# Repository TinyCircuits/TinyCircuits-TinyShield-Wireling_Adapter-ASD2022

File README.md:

# TinyCircuits TinyShield Wireling Adapter ASD2022
# ASD2022 Rev4

The design files are located under design_files/ for the TinyCircuits ASD2022 Rev 4 PCB. This is a TinyShield that is meant to add 4 separately addressable Wireling Ports to any TinyDuino stack.

Format is in Cadsoft Eagle format - Eagle version 6.2 was used for the original design.

For more infomation on this, check out the product page at TinyCircuits.com

# License:

Design by TinyCircuits.
All design files are released under the Creative Commons Attribution Share-Alike 3.0 License, see the following link for details: http://creativecommons.org/licenses/by-sa/3.0

All text above must be included in any redistribution or derived design

This project uses designs and concepts developed as part of the Arduino project and the LilyPad project.  The TinyCircuits design files themselves (schematics, PCB and libraries) are not directly derived from these works' design files and have been created new, however the concepts and basic architecture behind the TinyDuino and TinyLily products are derived and we thank the hard work of the organizations below for their contributions to open-source hardware:
  
Original Arduino Uno Design by Team Arduino

LilyPad Arduino Design by Leah Buechley and Sparkfun Electronics

Please support the open-source hardware community

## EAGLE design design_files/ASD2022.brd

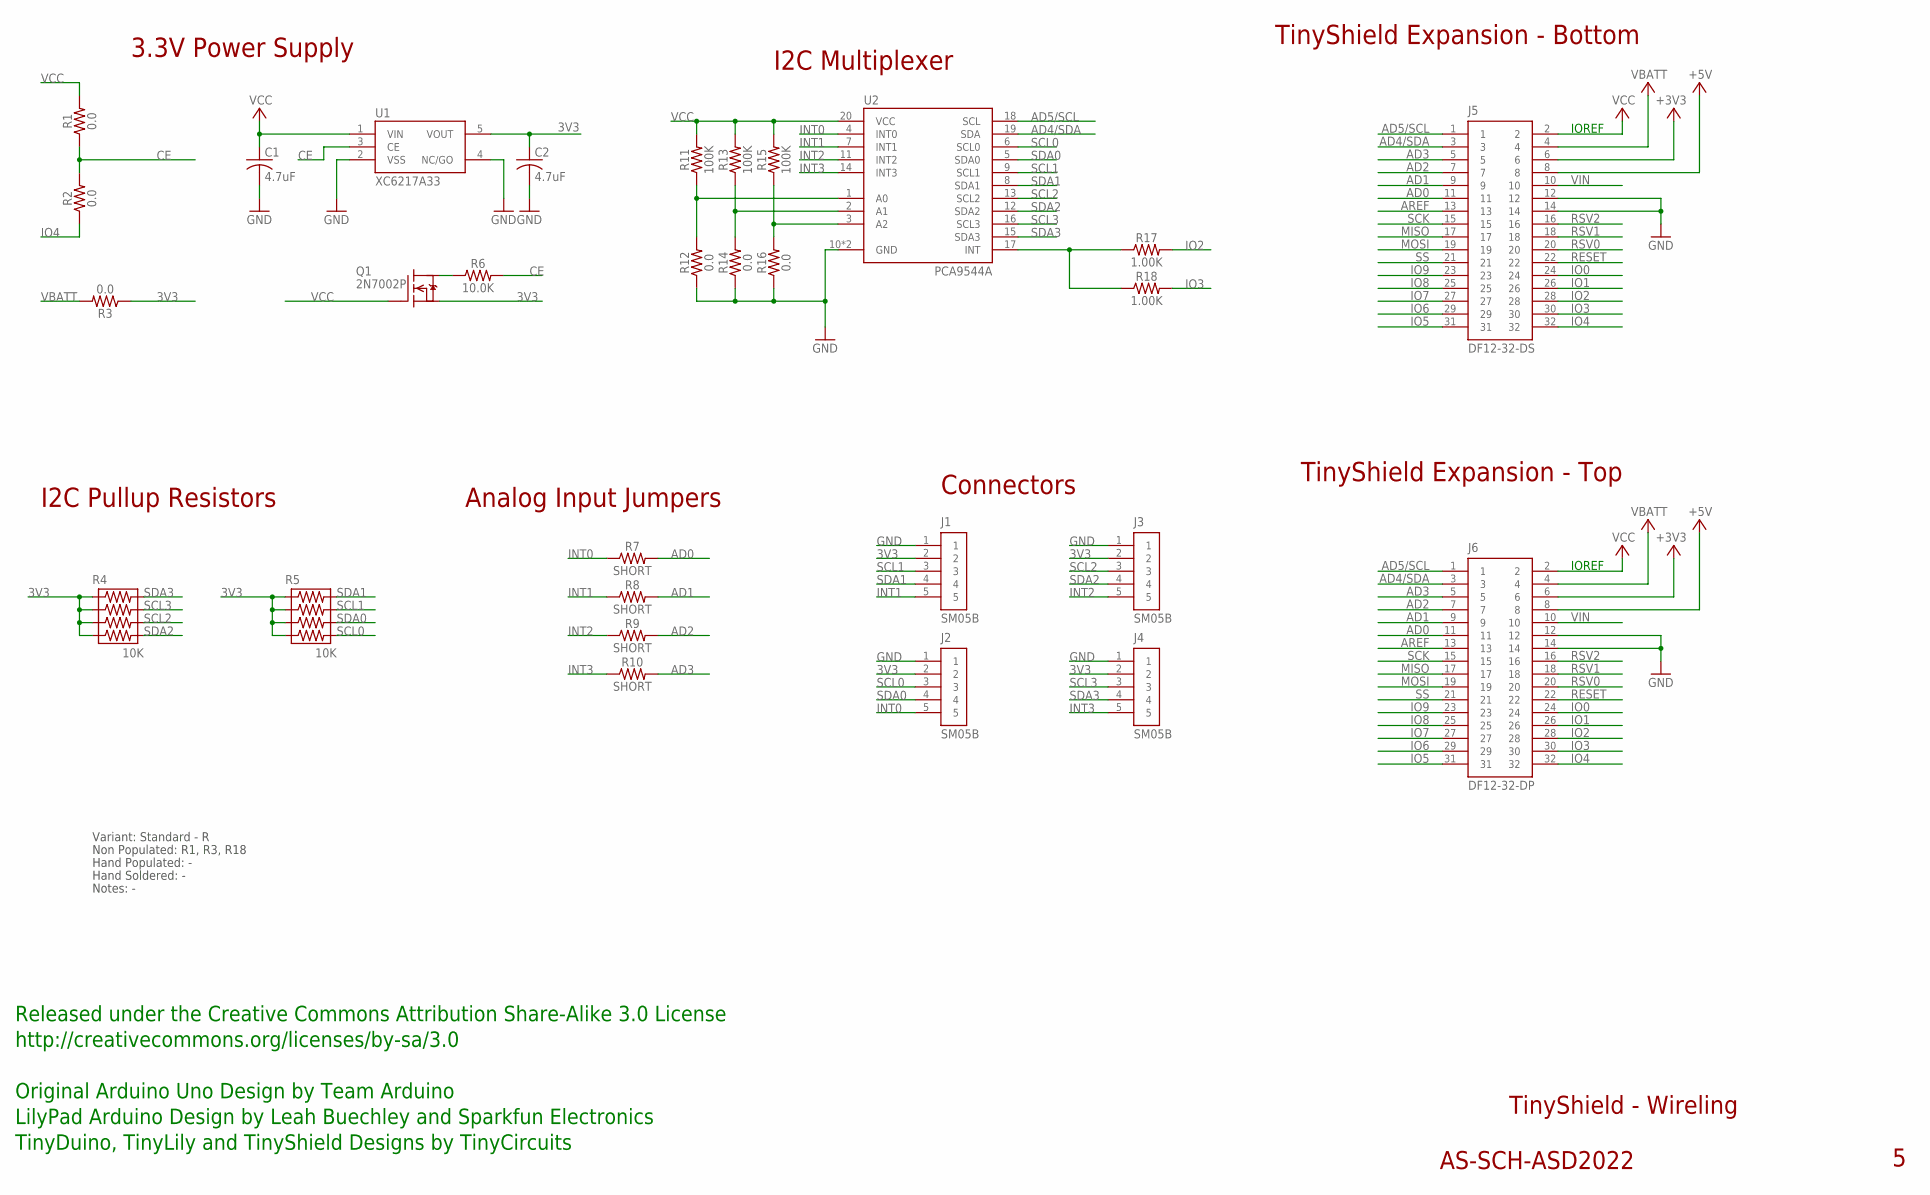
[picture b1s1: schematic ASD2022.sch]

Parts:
C1, C2: 4.7uF; C0402; PARTNO AS-ITM-00242
J1, J2, J3, J4: SM05B; JST_SH_5X1_EDGE
J5: DF12-32-DS; PARTNO AS-ITM-00012
J6: DF12-32-DP; PARTNO AS-ITM-00015
Q1: 2N7002P; SOT-416; PARTNO AS-ITM-00110
R1, R2, R3, R12, R14, R16: 0.0; 0402; PARTNO AS-ITM-00076
R4, R5: 10K; 0402RPACK; PARTNO AS-ITM-00520
R6: 10.0K; 0402; PARTNO AS-ITM-00032
R7, R8, R9, R10: SHORT; 0402_SHORT
R11, R13, R15: 100K; 0402; PARTNO AS-ITM-00004
R17, R18: 1.00K; 0402
U1: XC6217A33; SOT-25; PARTNO AS-ITM-00249
U2: PCA9544A; VQFN-20_4.5X3.5

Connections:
3V3: C2.1, J1.2, J2.2, J3.2, J4.2, Q1.2 (S), R3.1, R4.1, R4.3, R4.5, R4.7, R5.1, R5.3, R5.5, R5.7, U1.5 (VOUT)
+3V3: J5.6, J6.6
+5V: J5.8, J6.8
AD0: J5.11, J6.11, R7.2
AD1: J5.9, J6.9, R8.2
AD2: J5.7, J6.7, R9.2
AD3: J5.5, J6.5, R10.2
AD4/SDA: J5.3, J6.3, U2.19 (SDA)
AD5/SCL: J5.1, J6.1, U2.18 (SCL)
AREF: J5.13, J6.13
CE: R1.1, R2.2, R6.2, U1.3 (CE)
GND: C1.2, C2.2, J1.1, J2.1, J3.1, J4.1, J5.12, J5.14, J6.12, J6.14, R12.1, R14.1, R16.1, U1.2 (VSS), U1.4 (NC/GO), U2.10 (GND), U2.PAD (GND)
INT0: J2.5, R7.1, U2.4 (INT0)
INT1: J1.5, R8.1, U2.7 (INT1)
INT2: J3.5, R9.1, U2.11 (INT2)
INT3: J4.5, R10.1, U2.14 (INT3)
IO0: J5.24, J6.24
IO1: J5.26, J6.26
IO2: J5.28, J6.28, R17.2
IO3: J5.30, J6.30, R18.2
IO4: J5.32, J6.32, R2.1
IO5: J5.31, J6.31
IO6: J5.29, J6.29
IO7: J5.27, J6.27
IO8: J5.25, J6.25
IO9: J5.23, J6.23
MISO: J5.17, J6.17
MOSI: J5.19, J6.19
unnamed: Q1.3 (D), R6.1
unnamed: R11.1, R12.2, U2.1 (A0)
unnamed: R15.1, R16.2, U2.3 (A2)
unnamed: R17.1, R18.1, U2.17 (INT)
unnamed: R13.1, R14.2, U2.2 (A1)
RESET: J5.22, J6.22
RSV0: J5.20, J6.20
RSV1: J5.18, J6.18
RSV2: J5.16, J6.16
SCK: J5.15, J6.15
SCL0: J2.3, R5.8, U2.6 (SCL0)
SCL1: J1.3, R5.4, U2.9 (SCL1)
SCL2: J3.3, R4.6, U2.13 (SCL2)
SCL3: J4.3, R4.4, U2.16 (SCL3)
SDA0: J2.4, R5.6, U2.5 (SDA0)
SDA1: J1.4, R5.2, U2.8 (SDA1)
SDA2: J3.4, R4.8, U2.12 (SDA2)
SDA3: J4.4, R4.2, U2.15 (SDA3)
SS: J5.21, J6.21
VBATT: J5.4, J6.4, R3.2
VCC: C1.1, J5.2, J6.2, Q1.1 (G), R1.2, R11.2, R13.2, R15.2, U1.1 (VIN), U2.20 (VCC)
VIN: J5.10, J6.10

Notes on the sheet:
TinyShield Expansion - Bottom
TinyShield - Wireling
AS-SCH-ASD2022
TinyShield Expansion - Top
IOREF
Released under the Creative Commons Attribution Share-Alike 3.0 License
http://creativecommons.org/licenses/by-sa/3.0
LilyPad Arduino Design by Leah Buechley and Sparkfun Electronics
TinyDuino, TinyLily and TinyShield Designs by TinyCircuits
Original Arduino Uno Design by Team Arduino
3.3V Power Supply
I2C Multiplexer
Connectors
Analog Input Jumpers
I2C Pullup Resistors
Non Populated: R1, R3, R18
Hand Populated: -
Hand Soldered: -
Notes: -
Variant: Standard - R

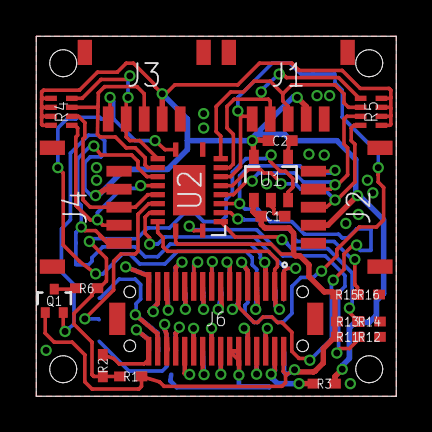
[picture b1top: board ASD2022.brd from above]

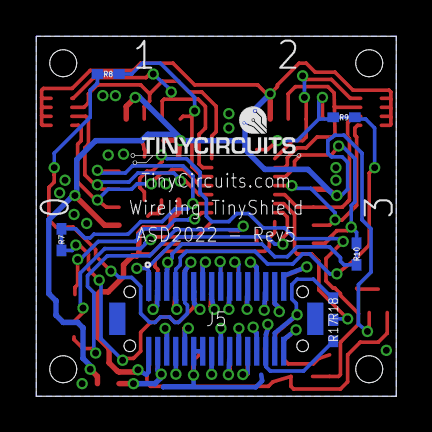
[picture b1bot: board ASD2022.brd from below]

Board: 2 copper layers, 20.0 x 20.0 mm, 30 parts (7 on the bottom side), 50 nets.

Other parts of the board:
U$1: DOCFIELD-TINYCIRCUITS-PCB

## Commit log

2019-10-22 init
2020-01-30 pics
2020-03-06 made labels red to make dark-mode friendly
2020-05-26 updated resistor numbers to match new schematic
2020-07-28 Add CAD data
2020-08-14 Update CAD drawing
